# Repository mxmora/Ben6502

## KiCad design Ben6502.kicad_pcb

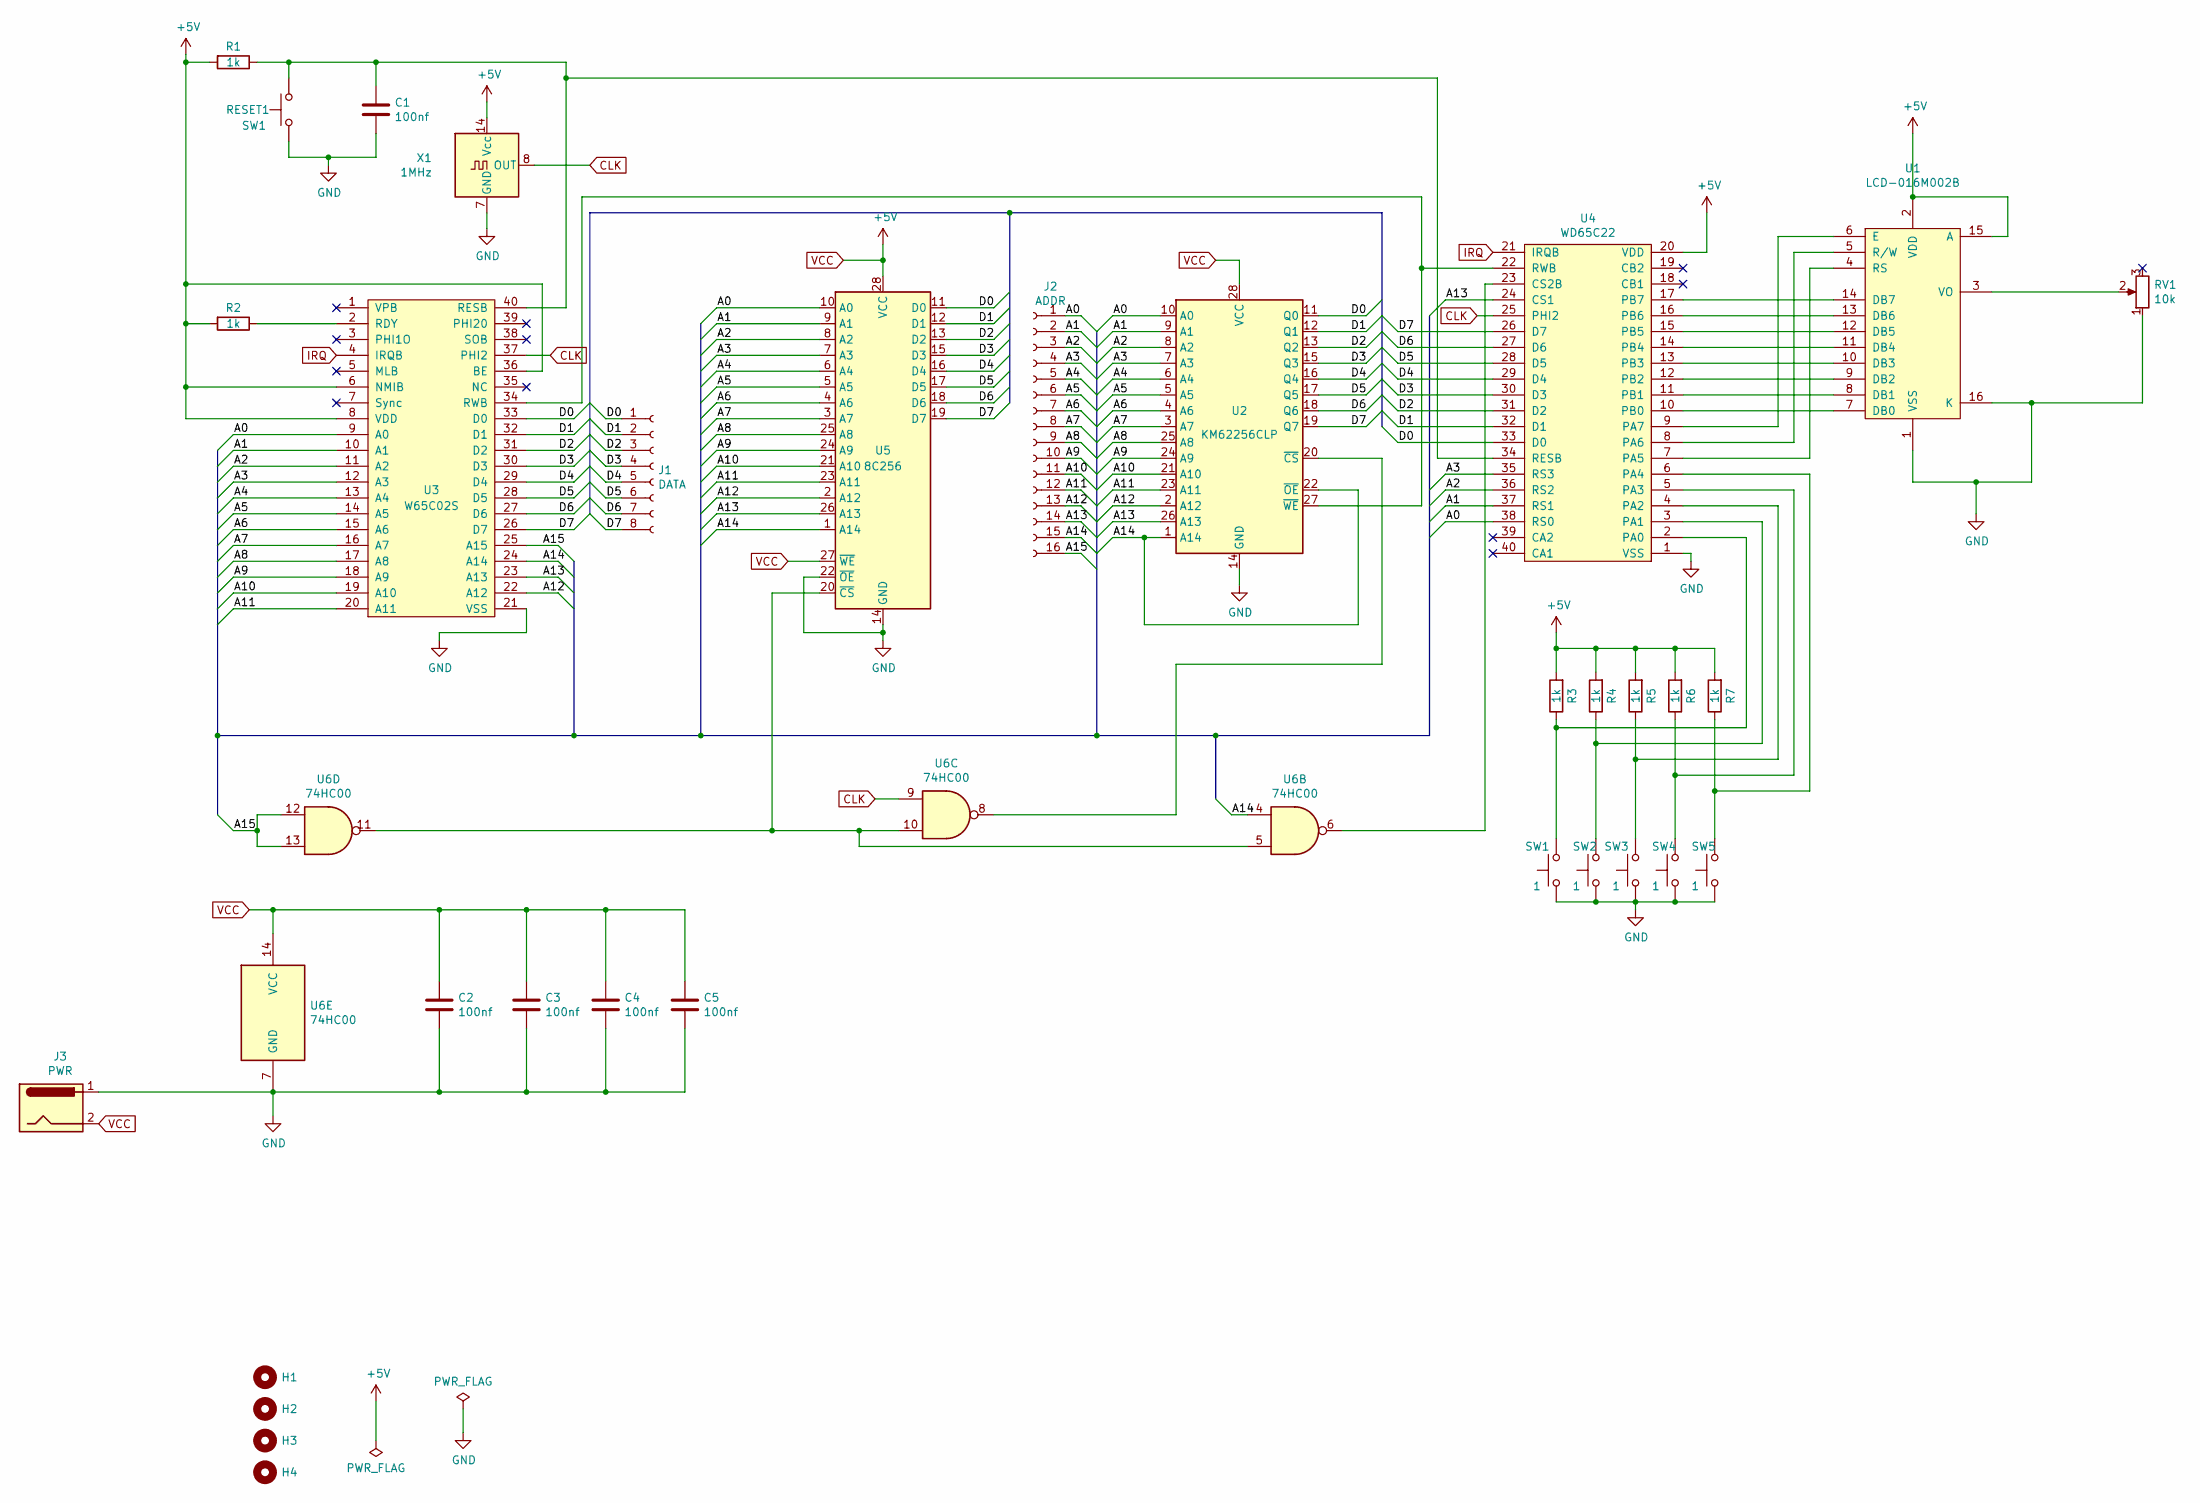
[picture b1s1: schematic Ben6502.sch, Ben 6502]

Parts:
C1, C2, C3, C4, C5: 100nf; C_Rect_L4.6mm_W2.0mm_P2.50mm_MKS02_FKP02
H1, H2, H3, H4: MountingHole; MountingHole_2.5mm
J1: DATA; PinSocket_1x08_P2.54mm_Vertical
J2: ADDR; PinSocket_1x16_P2.54mm_Vertical
J3: PWR; BarrelJack_CUI_PJ-063AH_Horizontal_CircularHoles
R1, R2, R3, R4, R5, R6, R7: 1k; R_Axial_DIN0204_L3.6mm_D1.6mm_P7.62mm_Horizontal
RESET1: SW1; PinHeader_1x02_P2.54mm_Vertical
RV1: 10k; PinHeader_1x03_P2.54mm_Vertical
SW1, SW2, SW3, SW4, SW5: 1; PinHeader_1x02_P2.54mm_Vertical
U1: LCD-016M002B; PinHeader_1x16_P2.54mm_Vertical
U2: KM62256CLP; DIP-28_W15.24mm_Socket_LongPads
U3: W65C02S; DIP-40_W15.24mm_Socket_LongPads
U4: WD65C22; DIP-40_W15.24mm_Socket_LongPads
U5: 8C256; DIP-28_W15.24mm_Socket_LongPads
U6: 74HC00; DIP-14_W7.62mm_Socket_LongPads
X1: 1MHz; Oscillator_DIP-14

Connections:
/A0: J2.1, U2.10 (A0), U3.9 (A0), U4.38 (RS0), U5.10 (A0)
/A1: J2.2, U2.9 (A1), U3.10 (A1), U4.37 (RS1), U5.9 (A1)
/A2: J2.3, U2.8 (A2), U3.11 (A2), U4.36 (RS2), U5.8 (A2)
/A3: J2.4, U2.7 (A3), U3.12 (A3), U4.35 (RS3), U5.7 (A3)
/A4: J2.5, U2.6 (A4), U3.13 (A4), U5.6 (A4)
/A5: J2.6, U2.5 (A5), U3.14 (A5), U5.5 (A5)
/A6: J2.7, U2.4 (A6), U3.15 (A6), U5.4 (A6)
/A7: J2.8, U2.3 (A7), U3.16 (A7), U5.3 (A7)
/A8: J2.9, U2.25 (A8), U3.17 (A8), U5.25 (A8)
/A9: J2.10, U2.24 (A9), U3.18 (A9), U5.24 (A9)
/A10: J2.11, U2.21 (A10), U3.19 (A10), U5.21 (A10)
/A11: J2.12, U2.23 (A11), U3.20 (A11), U5.23 (A11)
/A12: J2.13, U2.2 (A12), U3.22 (A12), U5.2 (A12)
/A13: J2.14, U2.26 (A13), U3.23 (A13), U4.24 (CS1), U5.26 (A13)
/A14: J2.15, U2.1 (A14), U2.22 (~OE), U3.24 (A14), U5.1 (A14), U6.4
/A15: J2.16, U3.25 (A15), U6.12, U6.13
/D0: J1.1, U2.11 (Q0), U3.33 (D0), U4.33 (D0), U5.11 (D0)
/D1: J1.2, U2.12 (Q1), U3.32 (D1), U4.32 (D1), U5.12 (D1)
/D2: J1.3, U2.13 (Q2), U3.31 (D2), U4.31 (D2), U5.13 (D2)
/D3: J1.4, U2.15 (Q3), U3.30 (D3), U4.30 (D3), U5.15 (D3)
/D4: J1.5, U2.16 (Q4), U3.29 (D4), U4.29 (D4), U5.16 (D4)
/D5: J1.6, U2.17 (Q5), U3.28 (D5), U4.28 (D5), U5.17 (D5)
/D6: J1.7, U2.18 (Q6), U3.27 (D6), U4.27 (D6), U5.18 (D6)
/D7: J1.8, U2.19 (Q7), U3.26 (D7), U4.26 (D7), U5.19 (D7)
CLK: U3.37 (PHI2), U4.25 (PHI2), U6.9, X1.8 (OUT)
GND: C1.2, C2.2, C3.2, C4.2, C5.2, J3.1, RESET1.1, RV1.1, SW1.1, SW2.1, SW3.1, SW4.1, SW5.1, U1.1 (VSS), U1.16 (K), U2.14 (GND), U3.21 (VSS), U4.1 (VSS), U5.14 (GND), U5.22 (~OE), U6.7 (GND), X1.7 (GND)
IRQ: U3.4 (IRQB), U4.21 (IRQB)
unnamed: C1.1, R1.1, RESET1.2, U3.40 (RESB), U4.34 (RESB)
unnamed: R2.1, U3.2 (RDY)
unnamed: R3.1, SW1.2, U4.2 (PA0)
unnamed: R4.1, SW2.2, U4.3 (PA1)
unnamed: R5.1, SW3.2, U4.4 (PA2)
unnamed: R6.1, SW4.2, U4.5 (PA3)
unnamed: R7.1, SW5.2, U4.6 (PA4)
unnamed: RV1.2, U1.3 (VO)
unnamed: U1.4 (RS), U4.7 (PA5)
unnamed: U1.5 (R/W), U4.8 (PA6)
unnamed: U1.6 (E), U4.9 (PA7)
unnamed: U1.7 (DB0), U4.10 (PB0)
unnamed: U1.8 (DB1), U4.11 (PB1)
unnamed: U1.9 (DB2), U4.12 (PB2)
unnamed: U1.10 (DB3), U4.13 (PB3)
unnamed: U1.11 (DB4), U4.14 (PB4)
unnamed: U1.12 (DB5), U4.15 (PB5)
unnamed: U1.13 (DB6), U4.16 (PB6)
unnamed: U1.14 (DB7), U4.17 (PB7)
unnamed: U2.20 (~CS), U6.8
unnamed: U2.27 (~WE), U3.34 (RWB), U4.22 (RWB)
unnamed: U4.23 (CS2B), U6.6
unnamed: U5.20 (~CS), U6.5, U6.10, U6.11
VCC: C2.1, C3.1, C4.1, C5.1, J3.2, R1.2, R2.2, R3.2, R4.2, R5.2, R6.2, R7.2, U1.2 (VDD), U1.15 (A), U2.28 (VCC), U3.6 (NMIB), U3.8 (VDD), U3.36 (BE), U4.20 (VDD), U5.27 (~WE), U5.28 (VCC), U6.14 (VCC), X1.14 (Vcc)

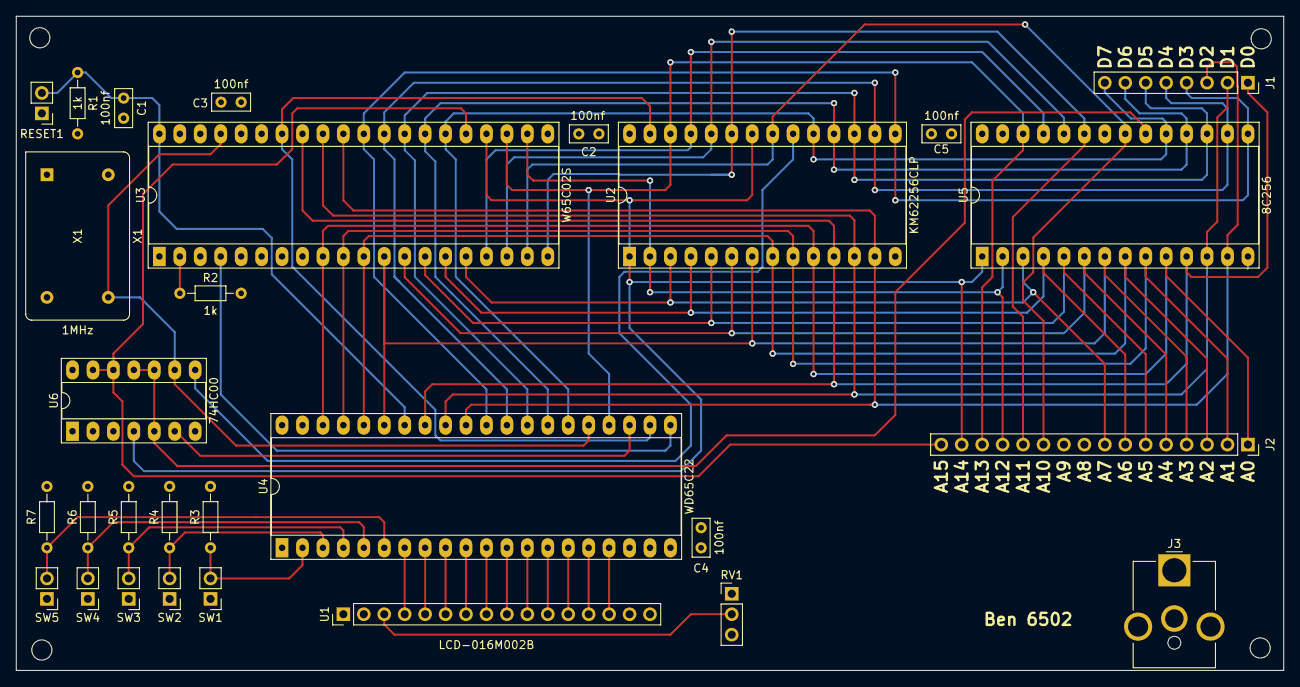
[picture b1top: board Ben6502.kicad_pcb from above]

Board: 4 copper layers, 157.5 x 81.3 mm, 33 parts (0 on the bottom side), 51 nets.

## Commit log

2020-12-19 First Check-in
2020-12-20 finish first pass
